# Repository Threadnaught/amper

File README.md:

# Amper

I'm unprivating my amper project for posterity. At time of writing, a lot of the code looks commented out and it's been like two years so I dare not go back in now. It's got two basic functions:

1. A learning tool for Op-Amps allowing you to set two voltage rails and create a circuit on the breadboard-like arangement of headers in the middle.
2. A (somewhat bad) dual rail switch mode lab supply

1 worked relatively well. Turns out pin headers are designed more for du-pont style pins than resistor or capacitor legs.

Regarding 2, This project taught me a lesson: don't use a microcontroller to manage power rails unless you really know what you're doing. There are many things which can raise input impeadance too fast for a UC to notice, and then the rail will spike to supply voltage.

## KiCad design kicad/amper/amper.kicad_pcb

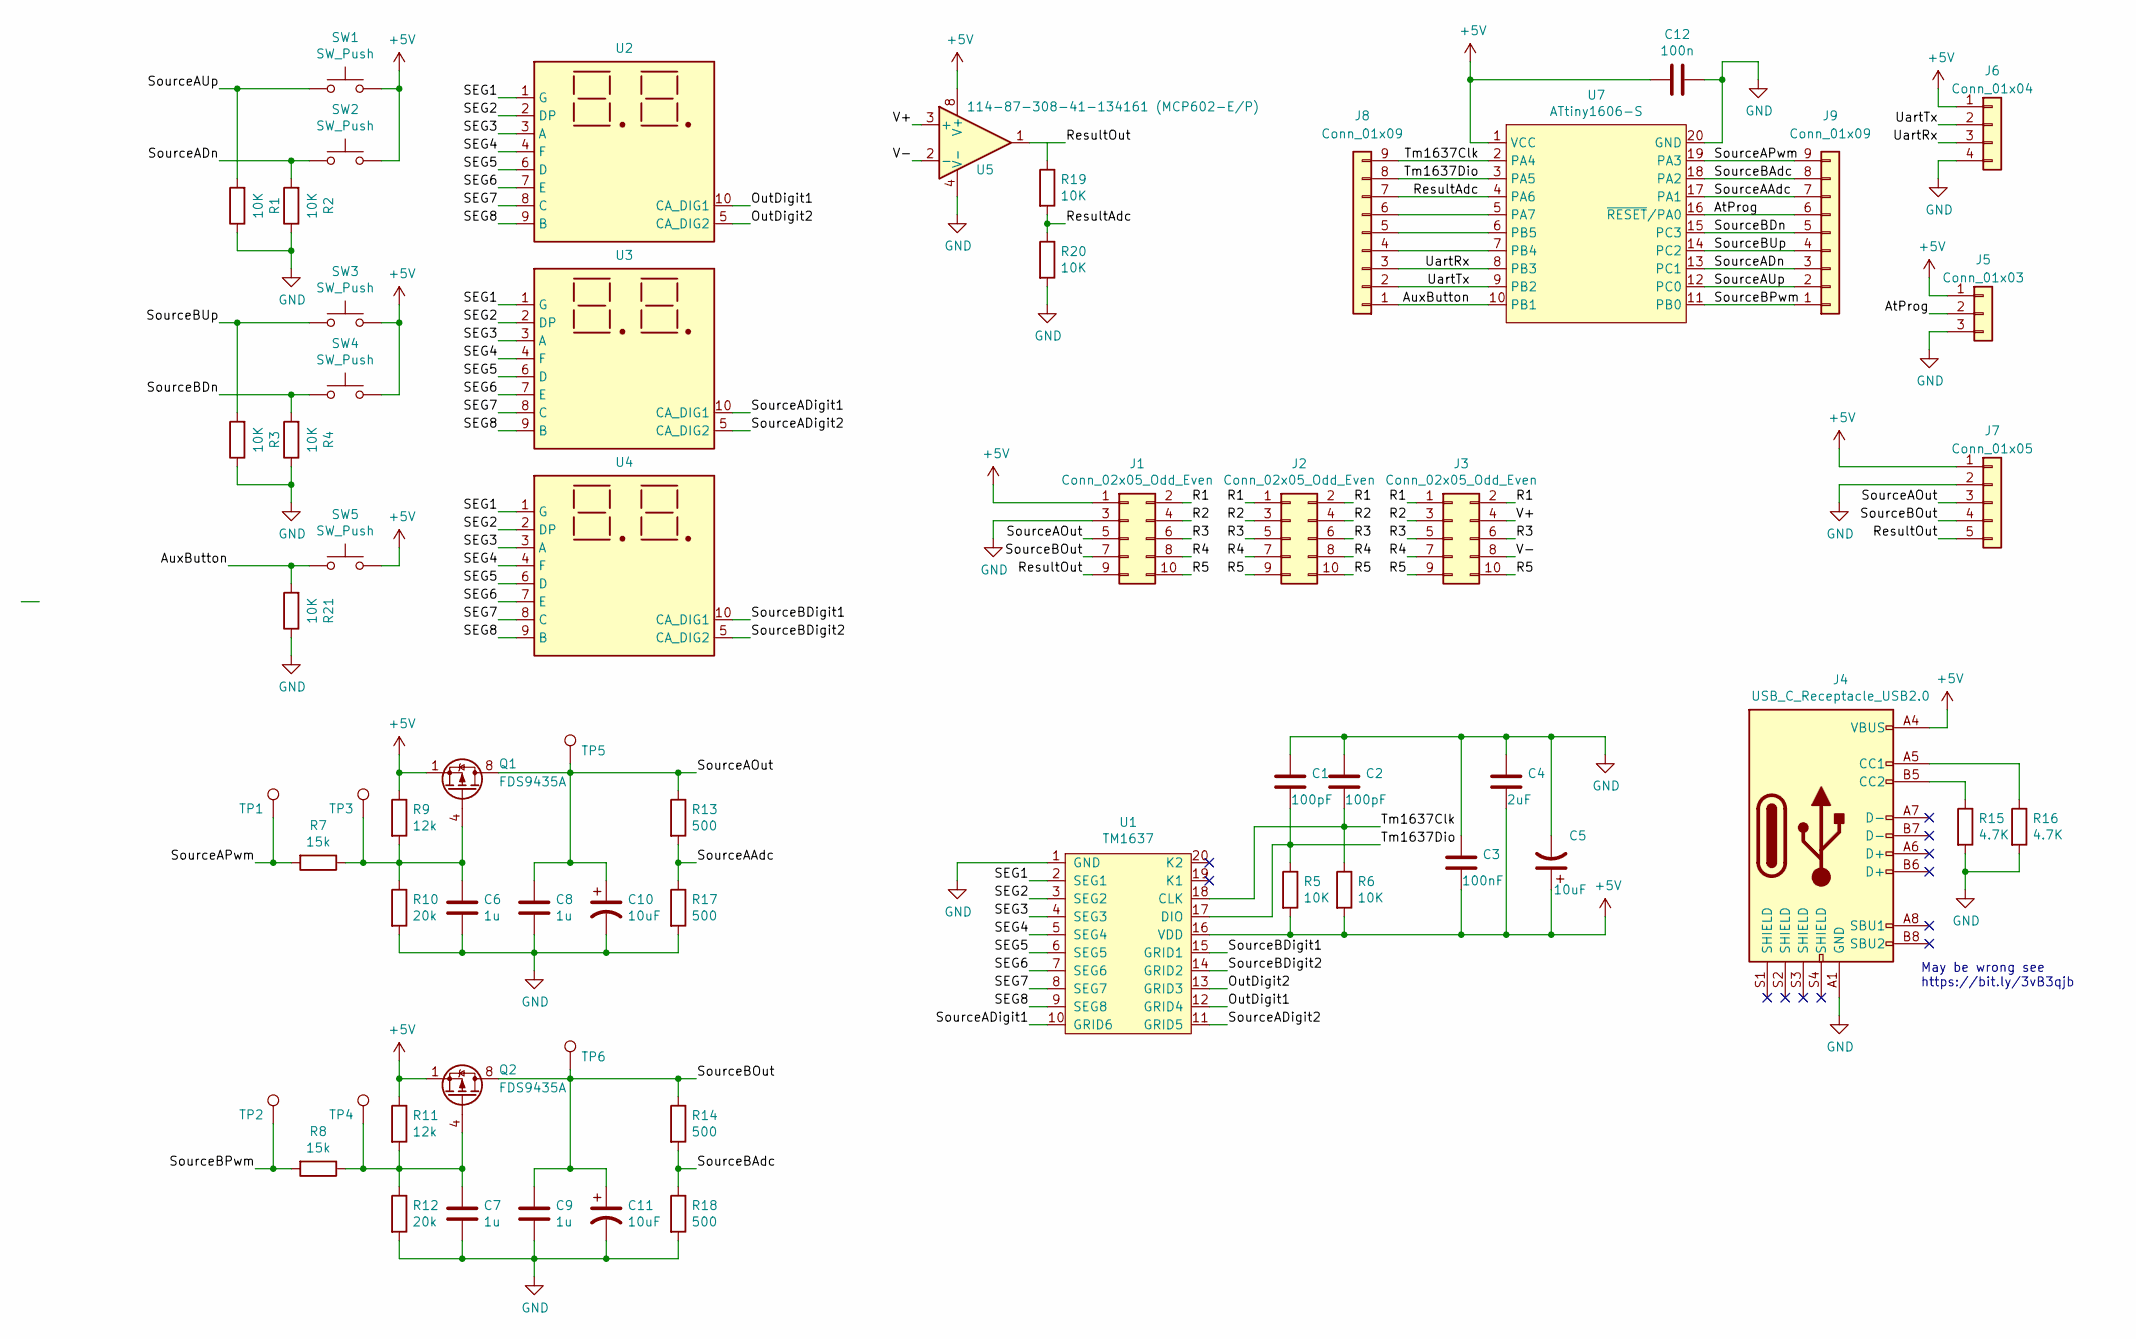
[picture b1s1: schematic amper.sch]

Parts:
C1, C2: 100pF; C_0603_1608Metric_Pad1.05x0.95mm_HandSolder
C3: 100nF; C_0603_1608Metric_Pad1.05x0.95mm_HandSolder
C4: 2uF; C_0603_1608Metric_Pad1.05x0.95mm_HandSolder; Part C85713
C5, C10, C11: 10uF; VT1H100M-CRD54; Part C305359
C6, C7, C8, C9: 1u; C_0603_1608Metric_Pad1.05x0.95mm_HandSolder
C12: 100n; C_0603_1608Metric_Pad1.05x0.95mm_HandSolder
J1: Conn_02x05_Odd_Even; 2.54_2x5_alternate-source-side
J2: Conn_02x05_Odd_Even; 2.54_2x5_alternate
J3: Conn_02x05_Odd_Even; 2.54_2x5_alternate-opamp-side
J4: USB_C_Receptacle_USB2.0; MC-303S
J5: Conn_01x03; PROG
J6: Conn_01x04; UART
J7: Conn_01x05; SolderHeader
J8, J9: Conn_01x09; PinSocket_1x09_P2.54mm_Vertical_no_silk
Q1, Q2: FDS9435A; SOIC-8_3.9x4.9mm_P1.27mm; Part C181098
R1, R2, R3, R4, R5, R6, R19, R20, R21: 10K; R_0603_1608Metric_Pad1.05x0.95mm_HandSolder
R7, R8: 15k; R_0603_1608Metric_Pad1.05x0.95mm_HandSolder
R9, R11: 12k; R_0603_1608Metric_Pad1.05x0.95mm_HandSolder
R10, R12: 20k; R_0603_1608Metric_Pad1.05x0.95mm_HandSolder
R13, R14, R17, R18: 500; R_0603_1608Metric_Pad1.05x0.95mm_HandSolder
R15, R16: 4.7K; R_0603_1608Metric_Pad1.05x0.95mm_HandSolder
SW1, SW3: SW_Push; UpSwitch; Part C2909692
SW2, SW4: SW_Push; DnSwitch; Part C2909692
SW5: SW_Push; K2-1157SP-I4SW-01; Part C2909692
TP1, TP2, TP3, TP4, TP5, TP6: TestPoint; TestPoint_Pad_D2.0mm
U1: TM1637; Part C20001
U2, U3, U4: HDSM-441B; SLS0392FB4A1GD; Part C226000
U5: 114-87-308-41-134161 (MCP602-E/P); 114-87-308-41-134161-generated
U7: ATtiny1606-S; SOIC-20W_7.5x12.8mm_P1.27mm

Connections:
+5V: C3.2, C4.2, C5.1, C12.2, J1.1, J4.A4 (VBUS), J4.A9 (VBUS), J4.B4 (VBUS), J4.B9 (VBUS), J5.1, J6.1, J7.1, Q1.1 (S), Q1.2 (S), Q1.3 (S), Q2.1 (S), Q2.2 (S), Q2.3 (S), R5.2, R6.2, R9.1, R11.1, SW1.2, SW2.2, SW3.2, SW4.2, SW5.2, U1.16 (VDD), U5.6 (NULL), U5.8 (V+), U7.1 (VCC)
/AtProg: J5.2, J9.6, U7.16 (~RESET~/PA0)
/AuxButton: J8.1, R21.2, SW5.1, U7.10 (PB1)
/OutDigit1: U1.12 (GRID4), U2.10 (CA_DIG1)
/OutDigit2: U1.13 (GRID3), U2.5 (CA_DIG2)
/R1: J1.2, J2.1, J2.2, J3.1, J3.2
/R2: J1.4, J2.3, J2.4, J3.3
/R3: J1.6, J2.5, J2.6, J3.5, J3.6
/R4: J1.8, J2.7, J2.8, J3.7
/R5: J1.10, J2.9, J2.10, J3.9, J3.10
/ResultAdc: J8.7, R19.2, R20.1, U7.4 (PA6)
/ResultOut: J1.9, J7.5, R19.1, U5.1
/SEG1: U1.2 (SEG1), U2.1 (G), U3.1 (G), U4.1 (G)
/SEG2: U1.3 (SEG2), U2.2 (DP), U3.2 (DP), U4.2 (DP)
/SEG3: U1.4 (SEG3), U2.3 (A), U3.3 (A), U4.3 (A)
/SEG4: U1.5 (SEG4), U2.4 (F), U3.4 (F), U4.4 (F)
/SEG5: U1.6 (SEG5), U2.6 (D), U3.6 (D), U4.6 (D)
/SEG6: U1.7 (SEG6), U2.7 (E), U3.7 (E), U4.7 (E)
/SEG7: U1.8 (SEG7), U2.8 (C), U3.8 (C), U4.8 (C)
/SEG8: U1.9 (SEG8), U2.9 (B), U3.9 (B), U4.9 (B)
/SourceAAdc: J9.7, R13.2, R17.1, U7.17 (PA1)
/SourceADigit1: U1.10 (GRID6), U3.10 (CA_DIG1)
/SourceADigit2: U1.11 (GRID5), U3.5 (CA_DIG2)
/SourceADn: J9.3, R2.2, SW2.1, U7.13 (PC1)
/SourceAOut: C8.1, C10.1, J1.5, J7.3, Q1.5 (D), Q1.6 (D), Q1.7 (D), Q1.8 (D), R13.1, TP5.1
/SourceAPwm: J9.9, R7.2, TP1.1, U7.19 (PA3)
/SourceAUp: J9.2, R1.2, SW1.1, U7.12 (PC0)
/SourceBAdc: J9.8, R14.2, R18.1, U7.18 (PA2)
/SourceBDigit1: U1.15 (GRID1), U4.10 (CA_DIG1)
/SourceBDigit2: U1.14 (GRID2), U4.5 (CA_DIG2)
/SourceBDn: J9.5, R4.2, SW4.1, U7.15 (PC3)
/SourceBOut: C9.1, C11.1, J1.7, J7.4, Q2.5 (D), Q2.6 (D), Q2.7 (D), Q2.8 (D), R14.1, TP6.1
/SourceBPwm: J9.1, R8.2, TP2.1, U7.11 (PB0)
/SourceBUp: J9.4, R3.2, SW3.1, U7.14 (PC2)
/Tm1637Clk: C2.2, J8.9, R6.1, U1.18 (CLK), U7.2 (PA4)
/Tm1637Dio: C1.2, J8.8, R5.1, U1.17 (DIO), U7.3 (PA5)
/UartRx: J6.3, J8.3, U7.8 (PB3)
/UartTx: J6.2, J8.2, U7.9 (PB2)
/V+: J3.4, U5.3 (+)
/V-: J3.8, U5.2 (-)
GND: C1.1, C2.1, C3.1, C4.1, C5.2, C6.2, C7.2, C8.2, C9.2, C10.2, C11.2, C12.1, J1.3, J4.A1 (GND), J4.A12 (GND), J4.B1 (GND), J4.B12 (GND), J5.3, J6.4, J7.2, R1.1, R2.1, R3.1, R4.1, R10.2, R12.2, R15.2, R16.2, R17.2, R18.2, R20.2, R21.1, U1.1 (GND), U5.4 (V-), U5.5 (NULL), U7.20 (GND)
unnamed: C6.1, Q1.4 (G), R7.1, R9.2, R10.1, TP3.1
unnamed: C7.1, Q2.4 (G), R8.1, R11.2, R12.1, TP4.1
unnamed: J4.A5 (CC1), R16.1
unnamed: J4.B5 (CC2), R15.1
unnamed: J8.4, U7.7 (PB4)
unnamed: J8.5, U7.6 (PB5)
unnamed: J8.6, U7.5 (PA7)

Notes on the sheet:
May be wrong see https://bit.ly/3vB3qjb

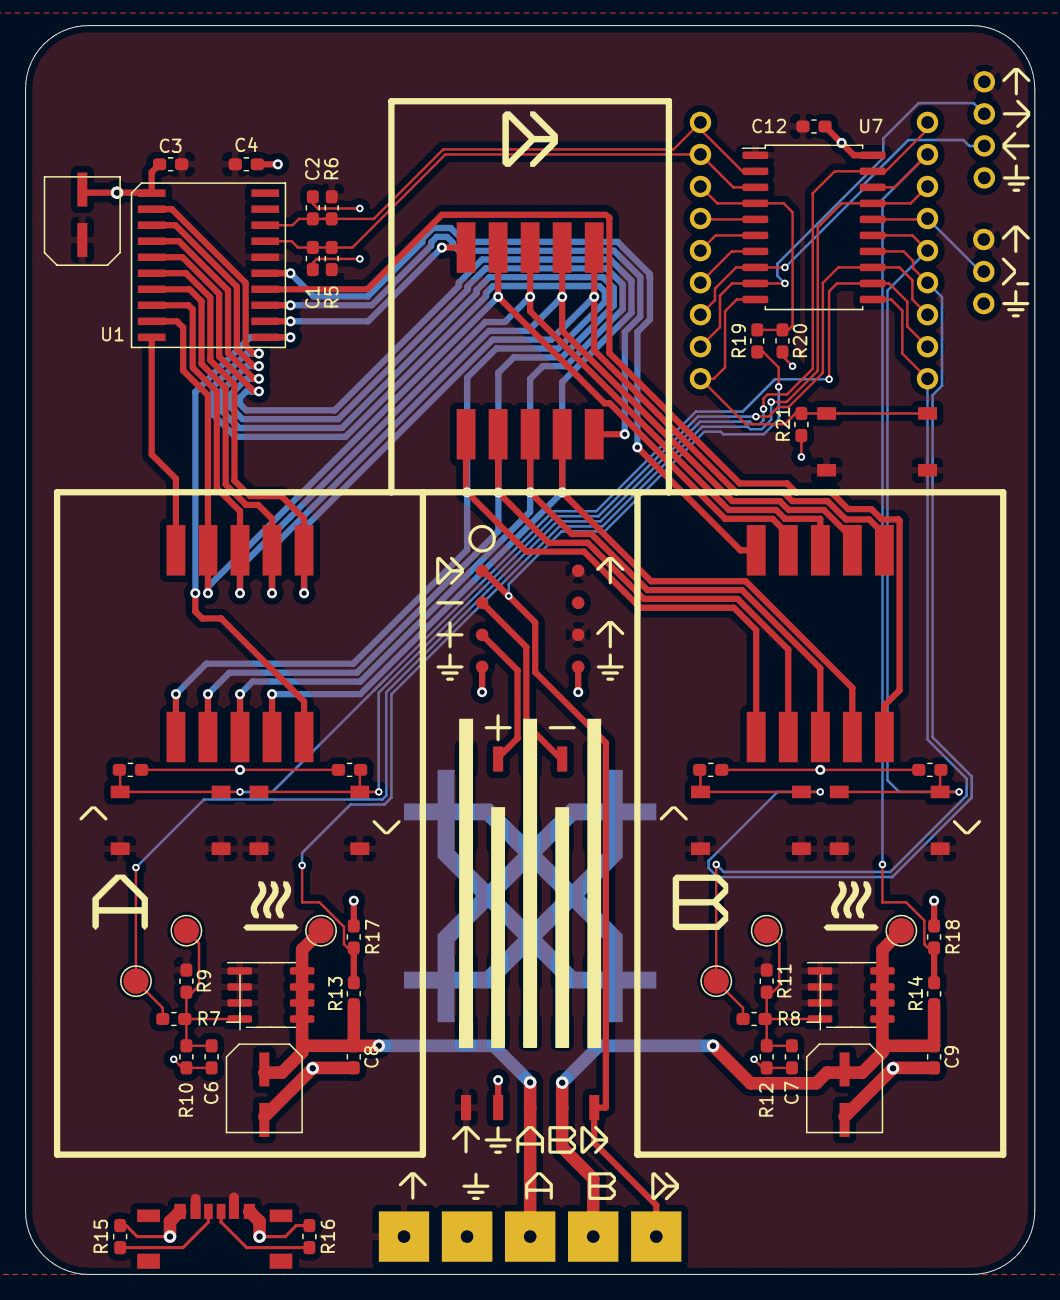
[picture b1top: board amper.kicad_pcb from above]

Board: 2 copper layers, 80.0 x 99.0 mm, 67 parts (1 on the bottom side), 48 nets.

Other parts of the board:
svg2mod, svg2mod#2: G***; LargeHeatWarning
svg2mod#3: G***; pcb_logo_small
svg2mod#4: G***; LargeOutput
svg2mod#5: G***; LargeB
svg2mod#6: G***; LargeA

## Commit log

2022-01-03 finished amper first version
2022-01-05 amper rev a
2022-01-06 Amper rev A ready to go
2022-02-06 TM1637 example code
2022-02-06 Added ASCII chars file (0-9) and a segment ordering scheme
2022-02-08 comment pass
2022-02-23 added easy fixes from testing to sch
2022-02-23 added attiny1606
2022-02-23 netlist rename pass
2022-02-23 added all connections from Amper 1606 port assignment in GDrive
2022-02-24 added breakout headers
2022-02-28 fixed library
2022-03-01 created new footprint for opamp breakout
2022-03-02 added solderable header + symbols
2022-03-03 Added new footprints for fat capacitor and usb-c socket
2022-03-03 Added mini breadboard
2022-03-03 ready for PCB layout
2022-03-04 Reannotated everything
2022-03-04 most of the large components in place, started laying tracks
2022-03-05 Layed out symetrical 7 seg and driver circuits
2022-03-05 added symbols, Routed very centre of board
2022-03-05 New layout with boxes
2022-03-05 Added USB socket and boxes with A, B and output symbols. Local routing started
2022-03-05 Added some very cool segment routing if I do say so myself
2022-03-05 Added grid routing
2022-03-06 Electrically connected, still needs some work
2022-03-06 misc corrections
2022-03-06 almost finished first path at board rev b, still a little work to do around logos, text and plane continuity
2022-03-06 Fixed a few issues, Ready for checking stage
2022-03-07 Rev B ready (?) for production
2022-03-20 rev B as fabbed
2022-03-20 added 1606 firmware
2022-03-20 forgot to add chars.h
2022-03-20 Added ADC code, butttons and integer comparison
2022-03-23 now displaying output of source B
2022-03-27 minimum viable power supply (single rail)
2022-03-28 first production version of software
2022-03-28 Ready for rev c
2022-03-29 Updated power supplies to schematic, reorganised schematic
2022-04-01 moved components to make better use of schematic
2022-04-01 Updated opamp
2022-04-01 high level schematic changes completed
2022-04-03 Rev C appears finished, going to sleep on it
2022-04-03 cleanup
2022-04-03 removed dead code
2022-04-04 added proportional error based feedback
2022-04-07 Added an extra button to the pcb
2022-04-08 PCB tidy pass
2022-04-10 Plotted rev C
2022-04-10 Replotted rev C
2022-05-04 added a basic pwm interrupt, new folder structure
2022-05-06 next version of control algorithm, split into files
2023-12-13 added readme and license
